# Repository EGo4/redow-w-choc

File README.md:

# redow-w-choc
KiCad files for the wireles low profile key version of the redox keyboard (unofficial)

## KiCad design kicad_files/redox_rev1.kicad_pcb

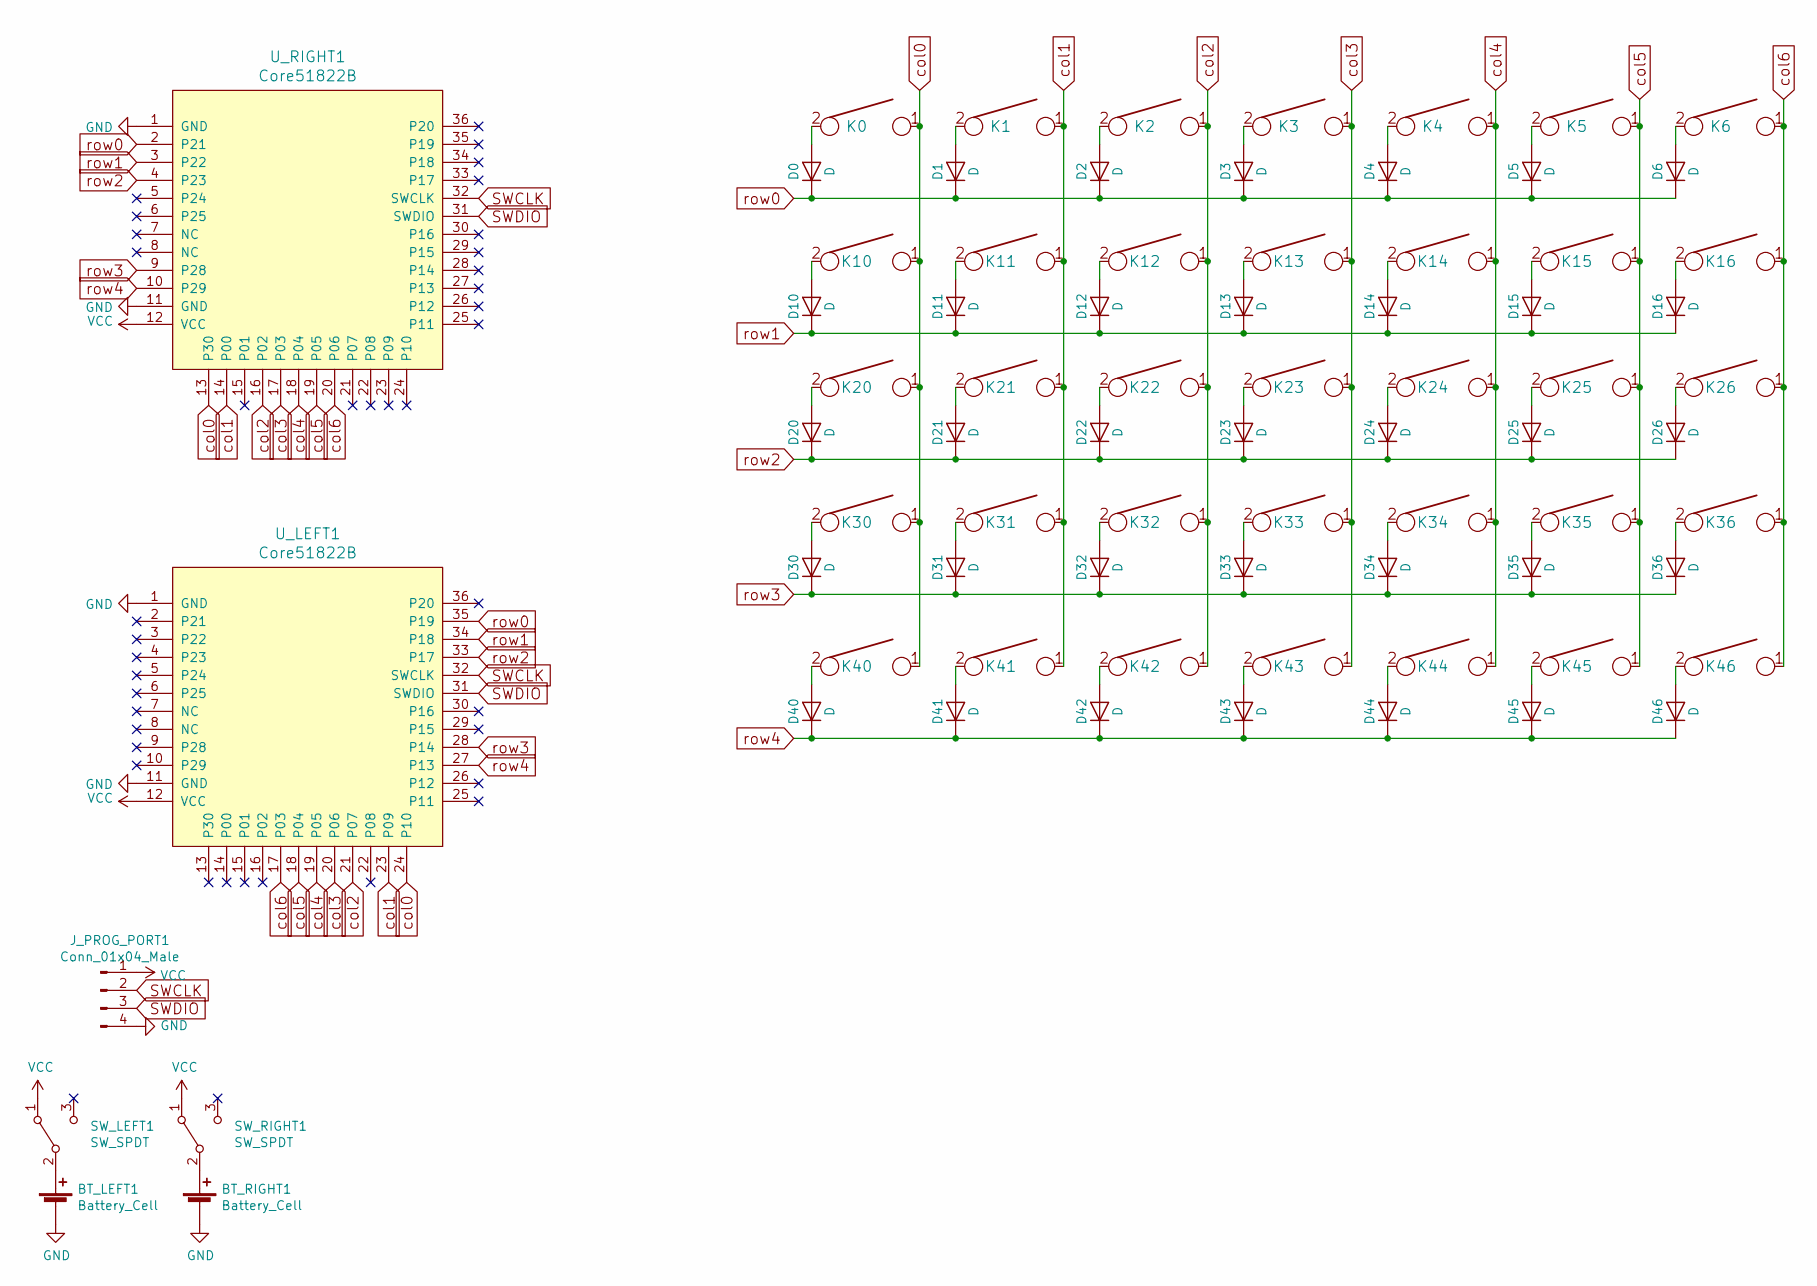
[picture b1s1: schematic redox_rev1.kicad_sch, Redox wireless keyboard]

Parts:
BT_LEFT1: Battery_Cell; BatteryHolder_Keystone_3034_1x20mm
BT_RIGHT1: Battery_Cell; BatteryHolder_Keystone_3034_1x20mm
D0, D1, D2, D3, D4, D5, D6, D10, D11, D12, D13, D14, D15, D16, D20, D21, D22, D23, D24, D25, D26, D30, D31, D32, D33, D34, D35, D36, D40, D41, D42, D43, D44, D45, D46: D; Diode-dual
J_PROG_PORT1: Conn_01x04_Male; PinHeader_1x04_P2.54mm_Vertical
K0, K10, K20, K30, K40, K44: KEYSW; Kailh_socket_PG1350_optional_reversible_125
K1, K2, K3, K4, K5, K6, K11, K12, K13, K14, K15, K21, K22, K23, K24, K25, K26, K31, K32, K33, K34, K35, K36, K41, K42, K43: KEYSW; Kailh_socket_PG1350_optional_reversible_100
K16, K45, K46: KEYSW; Kailh_socket_PG1350_optional_reversible_150
SW_LEFT1: SW_SPDT; SW_SPDT_CK-JS102011SAQN
SW_RIGHT1: SW_SPDT; SW_SPDT_CK-JS102011SAQN
U_LEFT1: Core51822B; MY-YJ-14015-Module
U_RIGHT1: Core51822B; MY-YJ-14015-Module

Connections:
GND: BT_LEFT1.2 (-), BT_RIGHT1.2 (-), J_PROG_PORT1.4, U_LEFT1.1 (GND), U_LEFT1.11 (GND), U_RIGHT1.1 (GND), U_RIGHT1.11 (GND)
unnamed: BT_LEFT1.1 (+), SW_LEFT1.2 (B)
unnamed: BT_RIGHT1.1 (+), SW_RIGHT1.2 (B)
unnamed: D0.2 (A), K0.2
unnamed: D1.2 (A), K1.2
unnamed: D2.2 (A), K2.2
unnamed: D3.2 (A), K3.2
unnamed: D4.2 (A), K4.2
unnamed: D5.2 (A), K5.2
unnamed: D6.2 (A), K6.2
unnamed: D10.2 (A), K10.2
unnamed: D11.2 (A), K11.2
unnamed: D12.2 (A), K12.2
unnamed: D13.2 (A), K13.2
unnamed: D14.2 (A), K14.2
unnamed: D15.2 (A), K15.2
unnamed: D16.2 (A), K16.2
unnamed: D20.2 (A), K20.2
unnamed: D21.2 (A), K21.2
unnamed: D22.2 (A), K22.2
unnamed: D23.2 (A), K23.2
unnamed: D24.2 (A), K24.2
unnamed: D25.2 (A), K25.2
unnamed: D26.2 (A), K26.2
unnamed: D30.2 (A), K30.2
unnamed: D31.2 (A), K31.2
unnamed: D32.2 (A), K32.2
unnamed: D33.2 (A), K33.2
unnamed: D34.2 (A), K34.2
unnamed: D35.2 (A), K35.2
unnamed: D36.2 (A), K36.2
unnamed: D40.2 (A), K40.2
unnamed: D41.2 (A), K41.2
unnamed: D42.2 (A), K42.2
unnamed: D43.2 (A), K43.2
unnamed: D44.2 (A), K44.2
unnamed: D45.2 (A), K45.2
unnamed: D46.2 (A), K46.2
SWCLK: J_PROG_PORT1.2, U_LEFT1.32 (SWCLK), U_RIGHT1.32 (SWCLK)
SWDIO: J_PROG_PORT1.3, U_LEFT1.31 (SWDIO), U_RIGHT1.31 (SWDIO)
VCC: J_PROG_PORT1.1, SW_LEFT1.1 (A), SW_RIGHT1.1 (A), U_LEFT1.12 (VCC), U_RIGHT1.12 (VCC)
col0: K0.1, K10.1, K20.1, K30.1, K40.1, U_LEFT1.24 (P10), U_RIGHT1.13 (P30)
col1: K1.1, K11.1, K21.1, K31.1, K41.1, U_LEFT1.23 (P09), U_RIGHT1.14 (P00)
col2: K2.1, K12.1, K22.1, K32.1, K42.1, U_LEFT1.21 (P07), U_RIGHT1.16 (P02)
col3: K3.1, K13.1, K23.1, K33.1, K43.1, U_LEFT1.20 (P06), U_RIGHT1.17 (P03)
col4: K4.1, K14.1, K24.1, K34.1, K44.1, U_LEFT1.19 (P05), U_RIGHT1.18 (P04)
col5: K5.1, K15.1, K25.1, K35.1, K45.1, U_LEFT1.18 (P04), U_RIGHT1.19 (P05)
col6: K6.1, K16.1, K26.1, K36.1, K46.1, U_LEFT1.17 (P03), U_RIGHT1.20 (P06)
row0: D0.1 (K), D1.1 (K), D2.1 (K), D3.1 (K), D4.1 (K), D5.1 (K), D6.1 (K), U_LEFT1.35 (P19), U_RIGHT1.2 (P21)
row1: D10.1 (K), D11.1 (K), D12.1 (K), D13.1 (K), D14.1 (K), D15.1 (K), D16.1 (K), U_LEFT1.34 (P18), U_RIGHT1.3 (P22)
row2: D20.1 (K), D21.1 (K), D22.1 (K), D23.1 (K), D24.1 (K), D25.1 (K), D26.1 (K), U_LEFT1.33 (P17), U_RIGHT1.4 (P23)
row3: D30.1 (K), D31.1 (K), D32.1 (K), D33.1 (K), D34.1 (K), D35.1 (K), D36.1 (K), U_LEFT1.28 (P14), U_RIGHT1.9 (P28)
row4: D40.1 (K), D41.1 (K), D42.1 (K), D43.1 (K), D44.1 (K), D45.1 (K), D46.1 (K), U_LEFT1.27 (P13), U_RIGHT1.10 (P29)

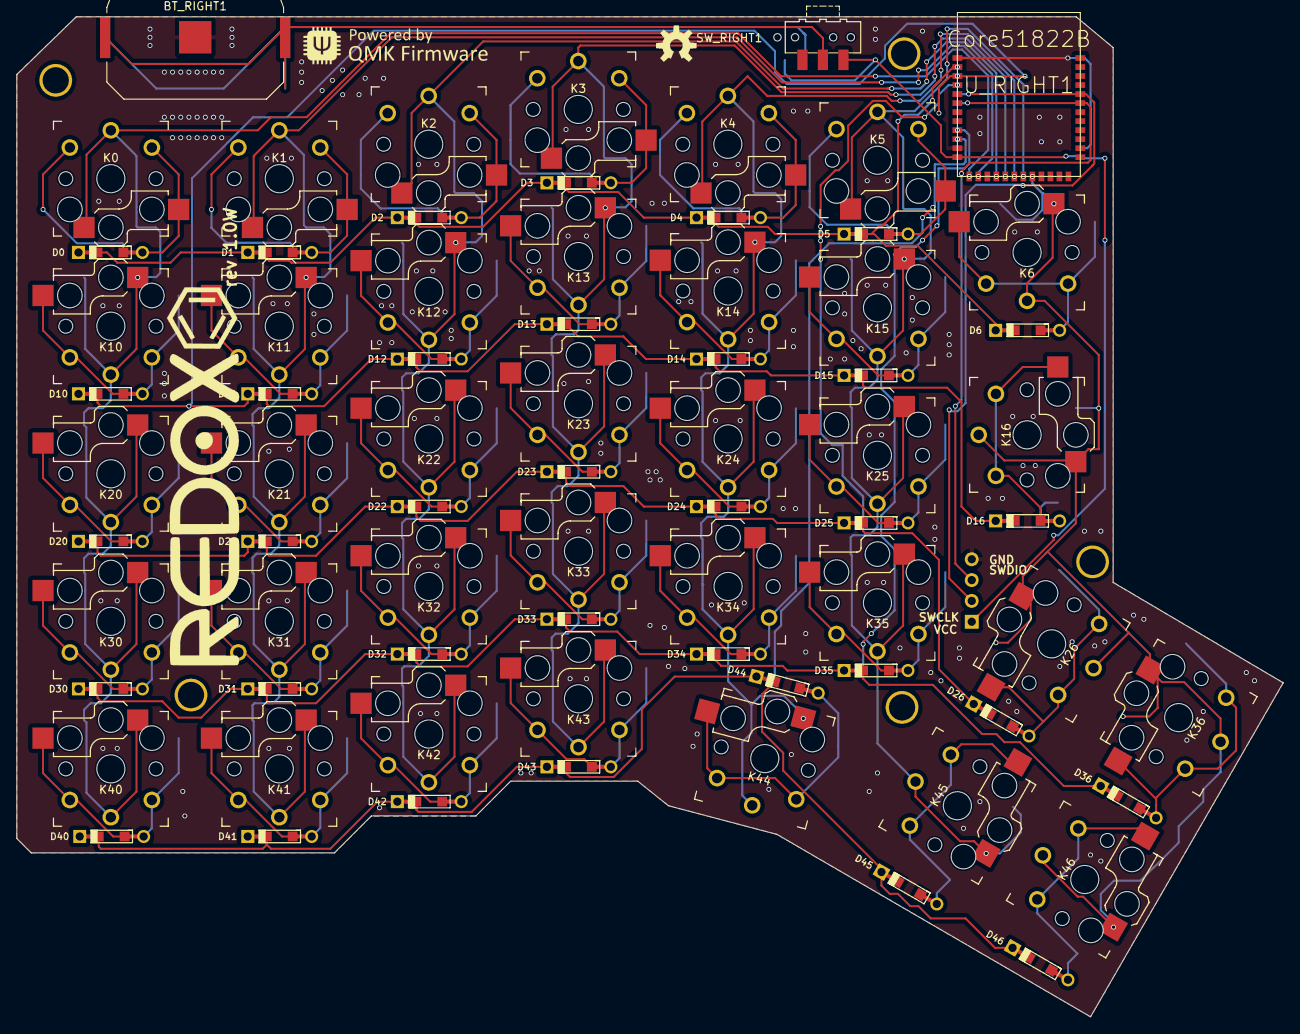
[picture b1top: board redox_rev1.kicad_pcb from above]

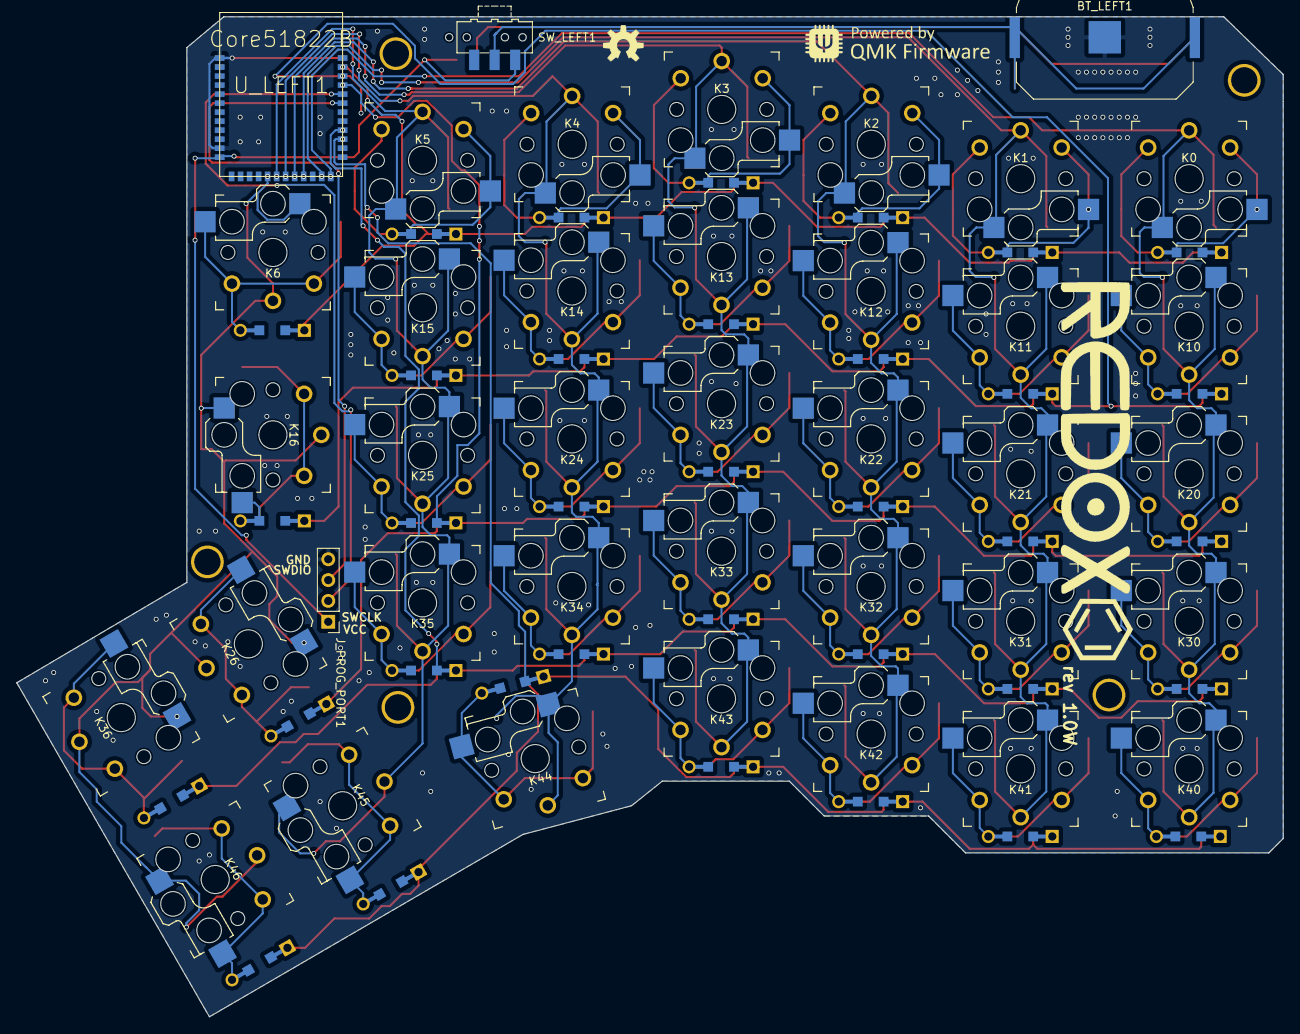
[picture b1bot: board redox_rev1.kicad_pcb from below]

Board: 2 copper layers, 154.5 x 122.0 mm, 82 parts (4 on the bottom side), 53 nets.

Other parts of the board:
HOLE_M3, HOLE_M3#2, HOLE_M3#3, HOLE_M3#4, HOLE_M3#5: VAL**; HOLE_M3

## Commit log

2023-04-22 Initial commit of redox wireles v1
2023-05-28 First production
    * NFSW GND not connected
